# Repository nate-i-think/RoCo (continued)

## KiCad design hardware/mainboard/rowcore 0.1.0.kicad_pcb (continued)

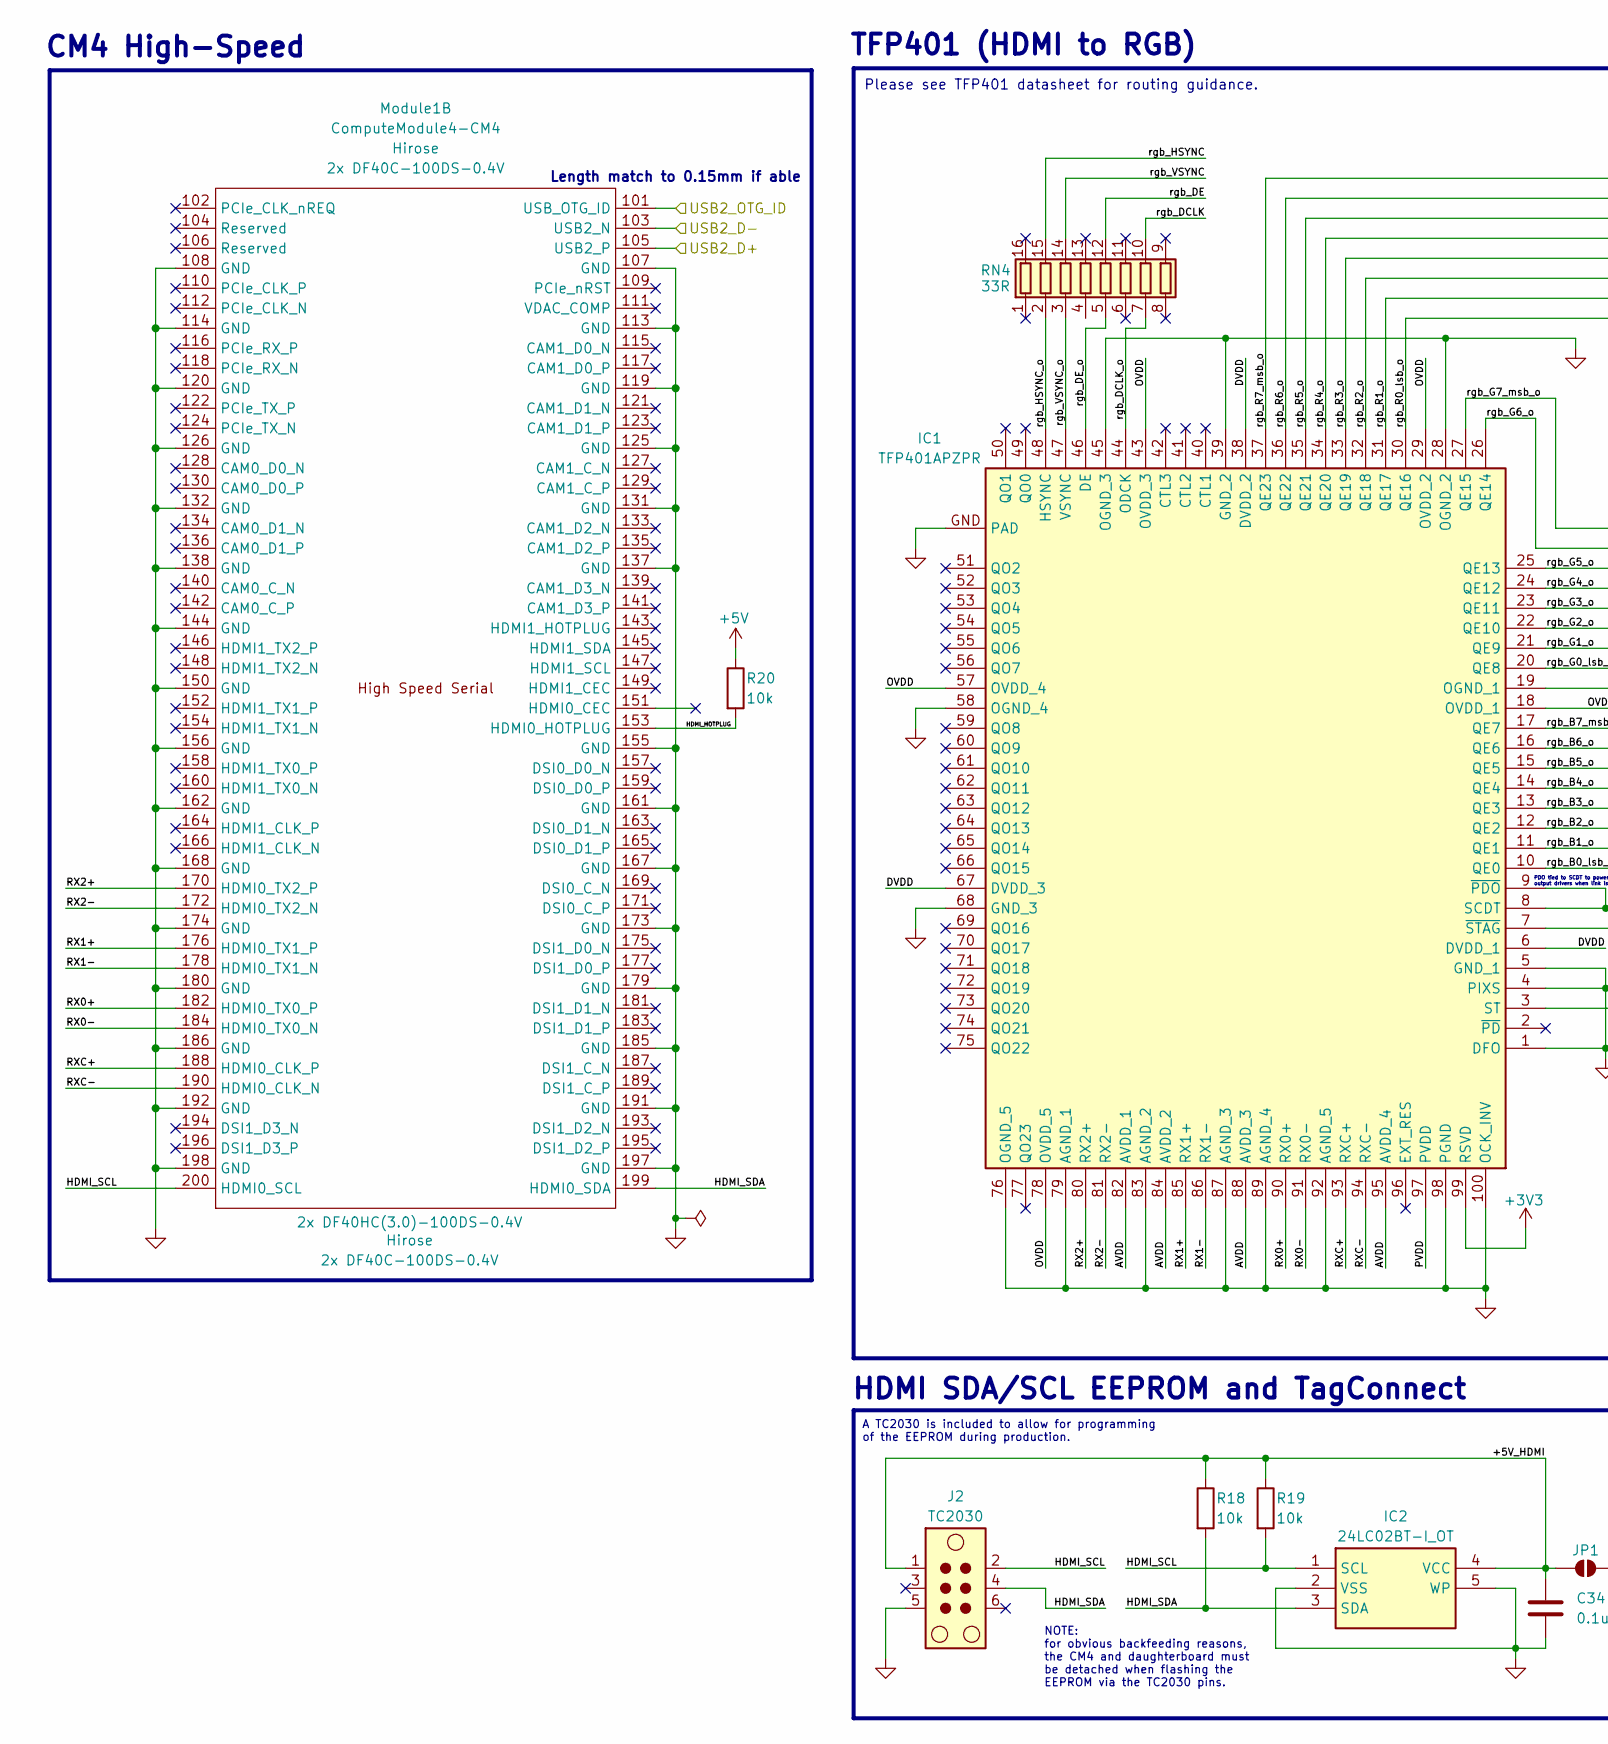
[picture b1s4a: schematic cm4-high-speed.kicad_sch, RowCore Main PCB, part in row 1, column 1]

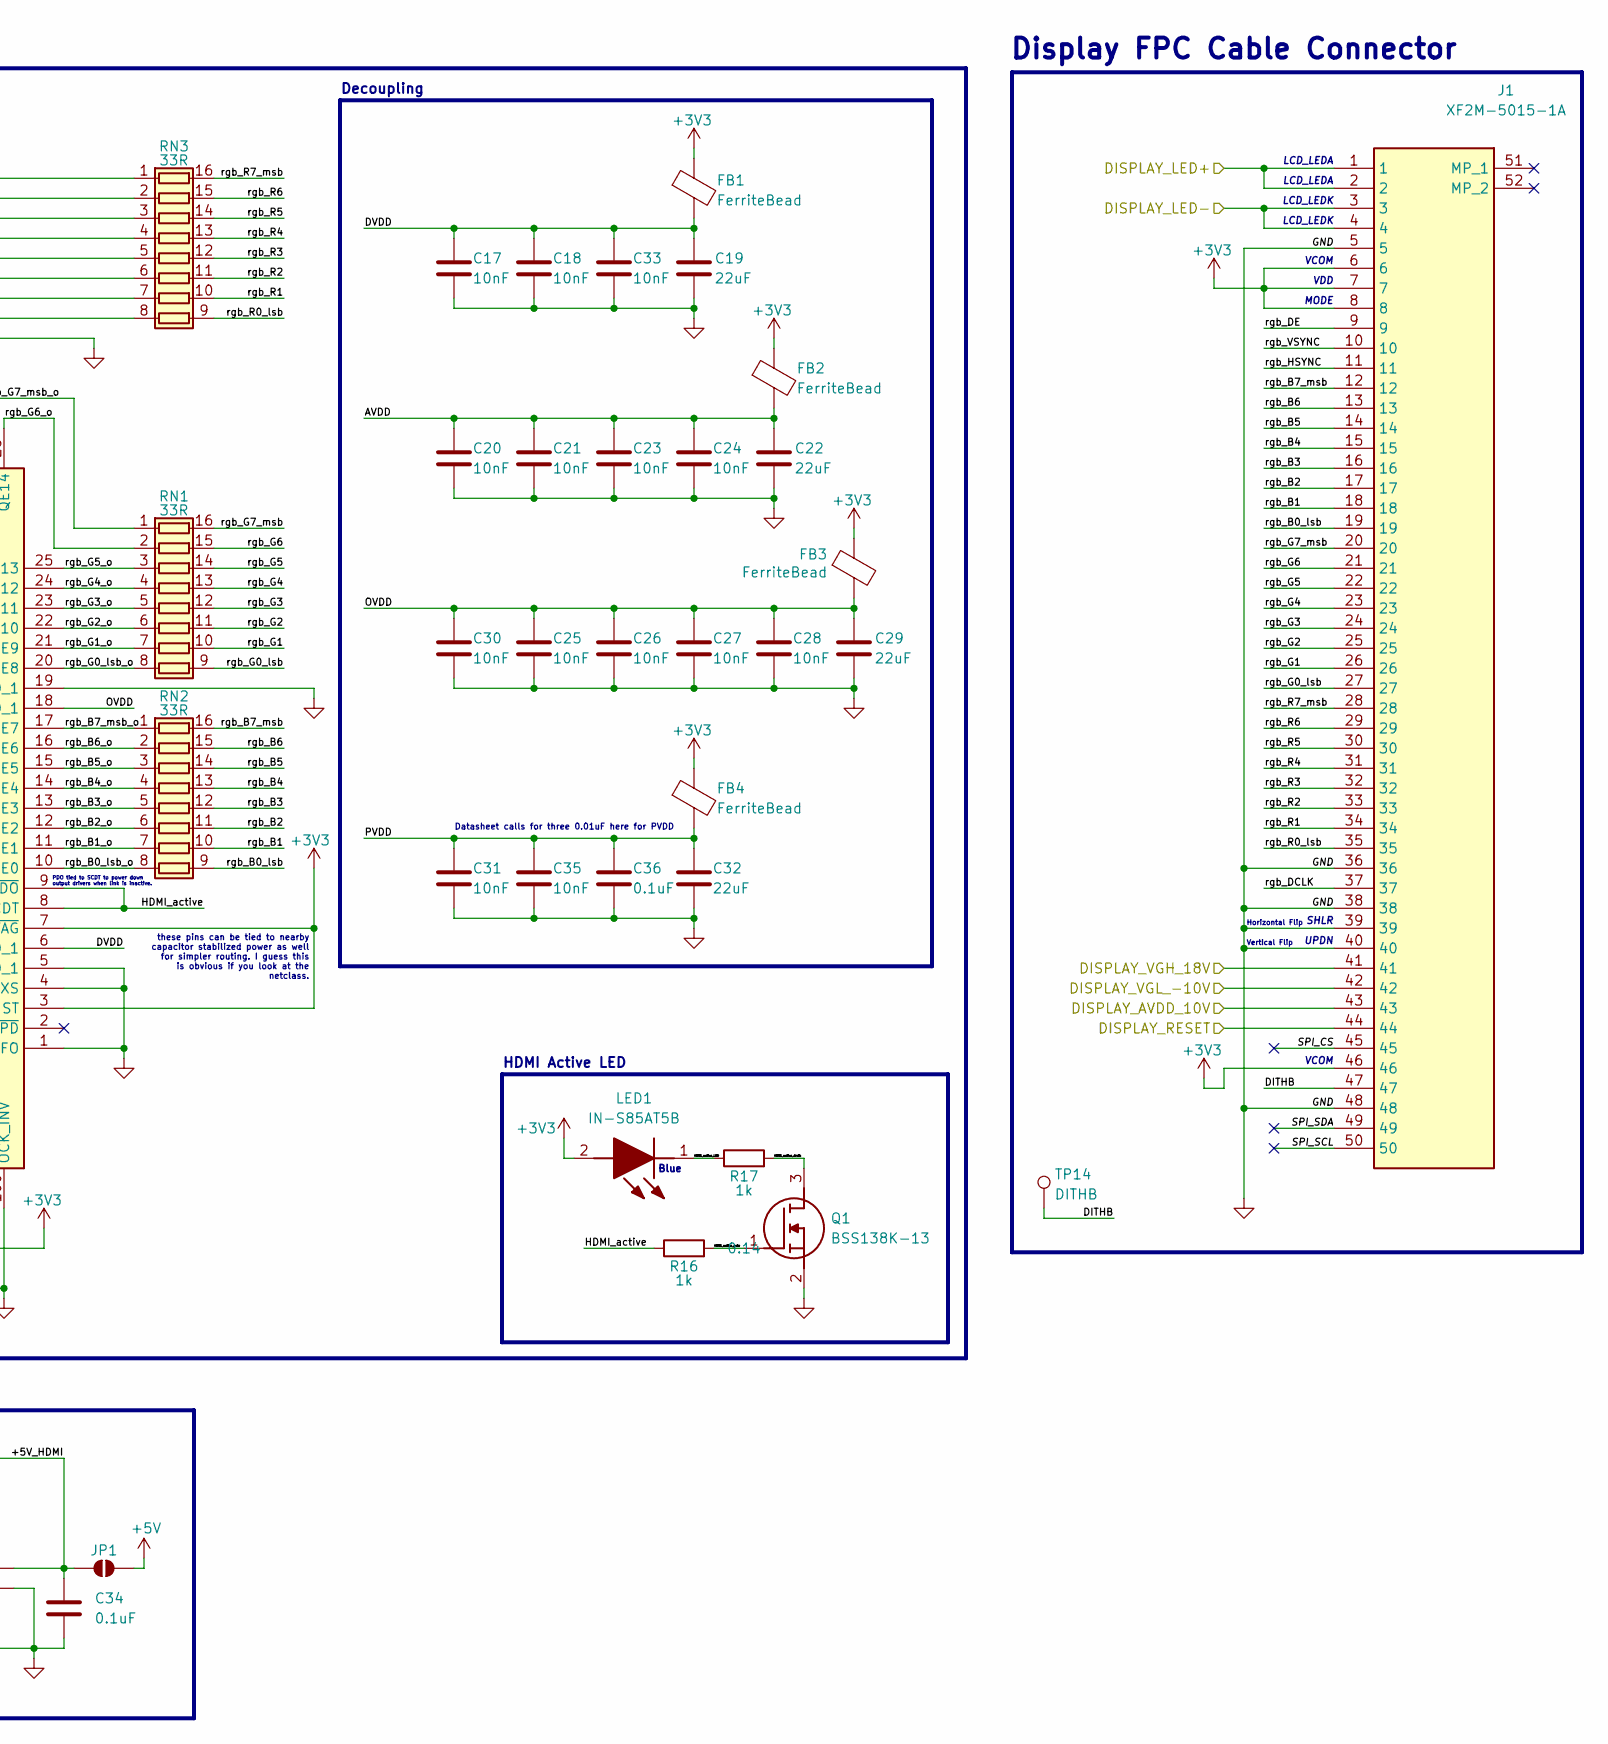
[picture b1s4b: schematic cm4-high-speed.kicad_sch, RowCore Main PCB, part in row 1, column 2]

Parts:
C17, C18, C20, C21, C23, C24, C25, C26, C27, C28, C30, C31, C33, C35: 10nF; C_0402_1005Metric
C19, C22, C29, C32: 22uF; C_1206_3216Metric
C34, C36: 0.1uF; C_0402_1005Metric
FB1, FB2, FB3, FB4: FerriteBead; BEADC1608X95N
IC1: TFP401APZPR; QFP50P1600X1600X120-100N; Mouser Part Number 595-TFP401APZPR
IC2: 24LC02BT-I_OT; SOT95P270X145-5N; Mouser Part Number 579-24LC02BT-I/OT
J1: XF2M-5015-1A; XF2M50151A; Mouser Part Number 653-XF2M-5015-1A
J2: TC2030; Tag-Connect_TC2030-IDC-NL_2x03_P1.27mm_Vertical
JP1: SolderJumper_2_Open; SolderJumper-2_P1.3mm_Open_RoundedPad1.0x1.5mm
LED1: IN-S85AT5B; LEDC2012X110N; Mouser Part Number 743-IN-S85AT5B
Module1: ComputeModule4-CM4; Raspberry-Pi-4-Compute-Module; MPN 2x DF40C-100DS-0.4V; Digi-Key_PN 2x H11615CT-ND
Q1: BSS138K-13; SOT96P240X110-3N; Mouser Part Number 621-BSS138K-13
R16, R17: 1k; R_0402_1005Metric
R18, R19, R20: 10k; R_0402_1005Metric
RN1, RN2, RN3, RN4: 33R; EXBU2H; Manufacturer Part Number EXB-U2H330JV
TP14: DITHB; TestPoint_Pad_D1.5mm

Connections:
+5V: JP1.1 (A), R20.1; also elsewhere on the board
/CM4 Lite GPIO/DISPLAY_RESET: J1.44; also elsewhere on the board
/CM4 Lite High Speed/+5V_HDMI: C34.1, IC2.4 (VCC), J2.1, JP1.2 (B), R18.1, R19.1; also elsewhere on the board
/CM4 Lite High Speed/AVDD: C20.1, C21.1, C22.1, C23.1, C24.1, FB2.2, IC1.82 (AVDD_1), IC1.84 (AVDD_2), IC1.88 (AVDD_3), IC1.95 (AVDD_4)
/CM4 Lite High Speed/DISPLAY_LED+: J1.1, J1.2; also elsewhere on the board
/CM4 Lite High Speed/DISPLAY_LED-: J1.3, J1.4; also elsewhere on the board
/CM4 Lite High Speed/DISPLAY_VGH_18V: J1.41; also elsewhere on the board
/CM4 Lite High Speed/DISPLAY_VGL_-10V: J1.42; also elsewhere on the board
/CM4 Lite High Speed/DITHB: J1.47, TP14.1
/CM4 Lite High Speed/DVDD: C17.1, C18.1, C19.1, C33.1, FB1.2, IC1.6 (DVDD_1), IC1.38 (DVDD_2), IC1.67 (DVDD_3)
/CM4 Lite High Speed/HDMI_HOTPLUG: Module1.153 (HDMI0_HOTPLUG), R20.2
/CM4 Lite High Speed/HDMI_SCL: IC2.1 (SCL), J2.2, Module1.200 (HDMI0_SCL), R19.2; also elsewhere on the board
/CM4 Lite High Speed/HDMI_SDA: IC2.3 (SDA), J2.4, Module1.199 (HDMI0_SDA), R18.2; also elsewhere on the board
/CM4 Lite High Speed/HDMI_active: IC1.8 (SCDT), IC1.9 (~PDO), R16.1
/CM4 Lite High Speed/HDMI_active_LED: LED1.1 (K), R17.1
/CM4 Lite High Speed/HDMI_active_drain: Q1.3 (D), R17.2
/CM4 Lite High Speed/HDMI_active_gate: Q1.1 (G), R16.2
/CM4 Lite High Speed/OVDD: C25.1, C26.1, C27.1, C28.1, C29.1, C30.1, FB3.2, IC1.18 (OVDD_1), IC1.29 (OVDD_2), IC1.43 (OVDD_3), IC1.57 (OVDD_4), IC1.78 (OVDD_5)
/CM4 Lite High Speed/PVDD: C31.1, C32.1, C35.1, C36.1, FB4.2, IC1.97 (PVDD)
/CM4 Lite High Speed/RX0+: IC1.90 (RX0+), Module1.182 (HDMI0_TX0_P)
/CM4 Lite High Speed/RX0-: IC1.91 (RX0-), Module1.184 (HDMI0_TX0_N)
/CM4 Lite High Speed/RX1+: IC1.85 (RX1+), Module1.176 (HDMI0_TX1_P)
/CM4 Lite High Speed/RX1-: IC1.86 (RX1-), Module1.178 (HDMI0_TX1_N)
/CM4 Lite High Speed/RX2+: IC1.80 (RX2+), Module1.170 (HDMI0_TX2_P)
/CM4 Lite High Speed/RX2-: IC1.81 (RX2-), Module1.172 (HDMI0_TX2_N)
/CM4 Lite High Speed/RXC+: IC1.93 (RXC+), Module1.188 (HDMI0_CLK_P)
/CM4 Lite High Speed/RXC-: IC1.94 (RXC-), Module1.190 (HDMI0_CLK_N)
/CM4 Lite High Speed/SPI_CS: J1.45
/CM4 Lite High Speed/SPI_SCL: J1.50
/CM4 Lite High Speed/SPI_SDA: J1.49
/CM4 Lite High Speed/USB2_OTG_ID: Module1.101 (USB_OTG_ID)
/CM4 Lite High Speed/rgb_B0_lsb: J1.19, RN2.9 (R8.2)
/CM4 Lite High Speed/rgb_B0_lsb_o: IC1.10 (QE0), RN2.8 (R8.1)
/CM4 Lite High Speed/rgb_B1: J1.18, RN2.10 (R7.2)
/CM4 Lite High Speed/rgb_B1_o: IC1.11 (QE1), RN2.7 (R7.1)
/CM4 Lite High Speed/rgb_B2: J1.17, RN2.11 (R6.2)
/CM4 Lite High Speed/rgb_B2_o: IC1.12 (QE2), RN2.6 (R6.1)
/CM4 Lite High Speed/rgb_B3: J1.16, RN2.12 (R5.2)
/CM4 Lite High Speed/rgb_B3_o: IC1.13 (QE3), RN2.5 (R5.1)
/CM4 Lite High Speed/rgb_B4: J1.15, RN2.13 (R4.2)
/CM4 Lite High Speed/rgb_B4_o: IC1.14 (QE4), RN2.4 (R4.1)
/CM4 Lite High Speed/rgb_B5: J1.14, RN2.14 (R3.2)
/CM4 Lite High Speed/rgb_B5_o: IC1.15 (QE5), RN2.3 (R3.1)
/CM4 Lite High Speed/rgb_B6: J1.13, RN2.15 (R2.2)
/CM4 Lite High Speed/rgb_B6_o: IC1.16 (QE6), RN2.2 (R2.1)
/CM4 Lite High Speed/rgb_B7_msb: J1.12, RN2.16 (R1.2)
/CM4 Lite High Speed/rgb_B7_msb_o: IC1.17 (QE7), RN2.1 (R1.1)
/CM4 Lite High Speed/rgb_DCLK: J1.37, RN4.10 (R7.2)
/CM4 Lite High Speed/rgb_DCLK_o: IC1.44 (ODCK), RN4.7 (R7.1)
/CM4 Lite High Speed/rgb_DE: J1.9, RN4.12 (R5.2)
/CM4 Lite High Speed/rgb_DE_o: IC1.46 (DE), RN4.5 (R5.1)
/CM4 Lite High Speed/rgb_G0_lsb: J1.27, RN1.9 (R8.2)
/CM4 Lite High Speed/rgb_G0_lsb_o: IC1.20 (QE8), RN1.8 (R8.1)
/CM4 Lite High Speed/rgb_G1: J1.26, RN1.10 (R7.2)
/CM4 Lite High Speed/rgb_G1_o: IC1.21 (QE9), RN1.7 (R7.1)
/CM4 Lite High Speed/rgb_G2: J1.25, RN1.11 (R6.2)
/CM4 Lite High Speed/rgb_G2_o: IC1.22 (QE10), RN1.6 (R6.1)
/CM4 Lite High Speed/rgb_G3: J1.24, RN1.12 (R5.2)
/CM4 Lite High Speed/rgb_G3_o: IC1.23 (QE11), RN1.5 (R5.1)
/CM4 Lite High Speed/rgb_G4: J1.23, RN1.13 (R4.2)
/CM4 Lite High Speed/rgb_G4_o: IC1.24 (QE12), RN1.4 (R4.1)
/CM4 Lite High Speed/rgb_G5: J1.22, RN1.14 (R3.2)
/CM4 Lite High Speed/rgb_G5_o: IC1.25 (QE13), RN1.3 (R3.1)
/CM4 Lite High Speed/rgb_G6: J1.21, RN1.15 (R2.2)
/CM4 Lite High Speed/rgb_G6_o: IC1.26 (QE14), RN1.2 (R2.1)
/CM4 Lite High Speed/rgb_G7_msb: J1.20, RN1.16 (R1.2)
/CM4 Lite High Speed/rgb_G7_msb_o: IC1.27 (QE15), RN1.1 (R1.1)
/CM4 Lite High Speed/rgb_HSYNC: J1.11, RN4.15 (R2.2)
/CM4 Lite High Speed/rgb_HSYNC_o: IC1.48 (HSYNC), RN4.2 (R2.1)
/CM4 Lite High Speed/rgb_R0_lsb: J1.35, RN3.9 (R8.2)
/CM4 Lite High Speed/rgb_R0_lsb_o: IC1.30 (QE16), RN3.8 (R8.1)
/CM4 Lite High Speed/rgb_R1: J1.34, RN3.10 (R7.2)
/CM4 Lite High Speed/rgb_R1_o: IC1.31 (QE17), RN3.7 (R7.1)
/CM4 Lite High Speed/rgb_R2: J1.33, RN3.11 (R6.2)
/CM4 Lite High Speed/rgb_R2_o: IC1.32 (QE18), RN3.6 (R6.1)
/CM4 Lite High Speed/rgb_R3: J1.32, RN3.12 (R5.2)
/CM4 Lite High Speed/rgb_R3_o: IC1.33 (QE19), RN3.5 (R5.1)
/CM4 Lite High Speed/rgb_R4: J1.31, RN3.13 (R4.2)
/CM4 Lite High Speed/rgb_R4_o: IC1.34 (QE20), RN3.4 (R4.1)
/CM4 Lite High Speed/rgb_R5: J1.30, RN3.14 (R3.2)
/CM4 Lite High Speed/rgb_R5_o: IC1.35 (QE21), RN3.3 (R3.1)
/CM4 Lite High Speed/rgb_R6: J1.29, RN3.15 (R2.2)
/CM4 Lite High Speed/rgb_R6_o: IC1.36 (QE22), RN3.2 (R2.1)
/CM4 Lite High Speed/rgb_R7_msb: J1.28, RN3.16 (R1.2)
/CM4 Lite High Speed/rgb_R7_msb_o: IC1.37 (QE23), RN3.1 (R1.1)
/CM4 Lite High Speed/rgb_VSYNC: J1.10, RN4.14 (R3.2)
/CM4 Lite High Speed/rgb_VSYNC_o: IC1.47 (VSYNC), RN4.3 (R3.1)
/USB_D+: Module1.105 (USB2_P); also elsewhere on the board
/USB_D-: Module1.103 (USB2_N); also elsewhere on the board
/Voltage Generation/DISPLAY_AVDD_10V: J1.43; also elsewhere on the board

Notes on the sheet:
Vertical Flip
VDD
MODE
Datasheet calls for three 0.01uF here for PVDD
LCD_LEDA
VCOM
Blue
A TC2030 is included to allow for programming of the EEPROM during production.
PDO tied to SCDT to power down output drivers when link is inactive.
Please see TFP401 datasheet for routing guidance.
SHLR
Horizontal Flip
Display FPC Cable Connector
Length match to 0.15mm if able
TFP401 (HDMI to RGB)
LCD_LEDK
Decoupling
NOTE: for obvious backfeeding reasons, the CM4 and daughterboard must be detached when flashing the EEPROM via the TC2030 pins.
CM4 High-Speed
HDMI SDA/SCL EEPROM and TagConnect
HDMI Active LED
UPDN
these pins can be tied to nearby capacitor stabilized power as well for simpler routing. I guess this is obvious if you look at the netclass.

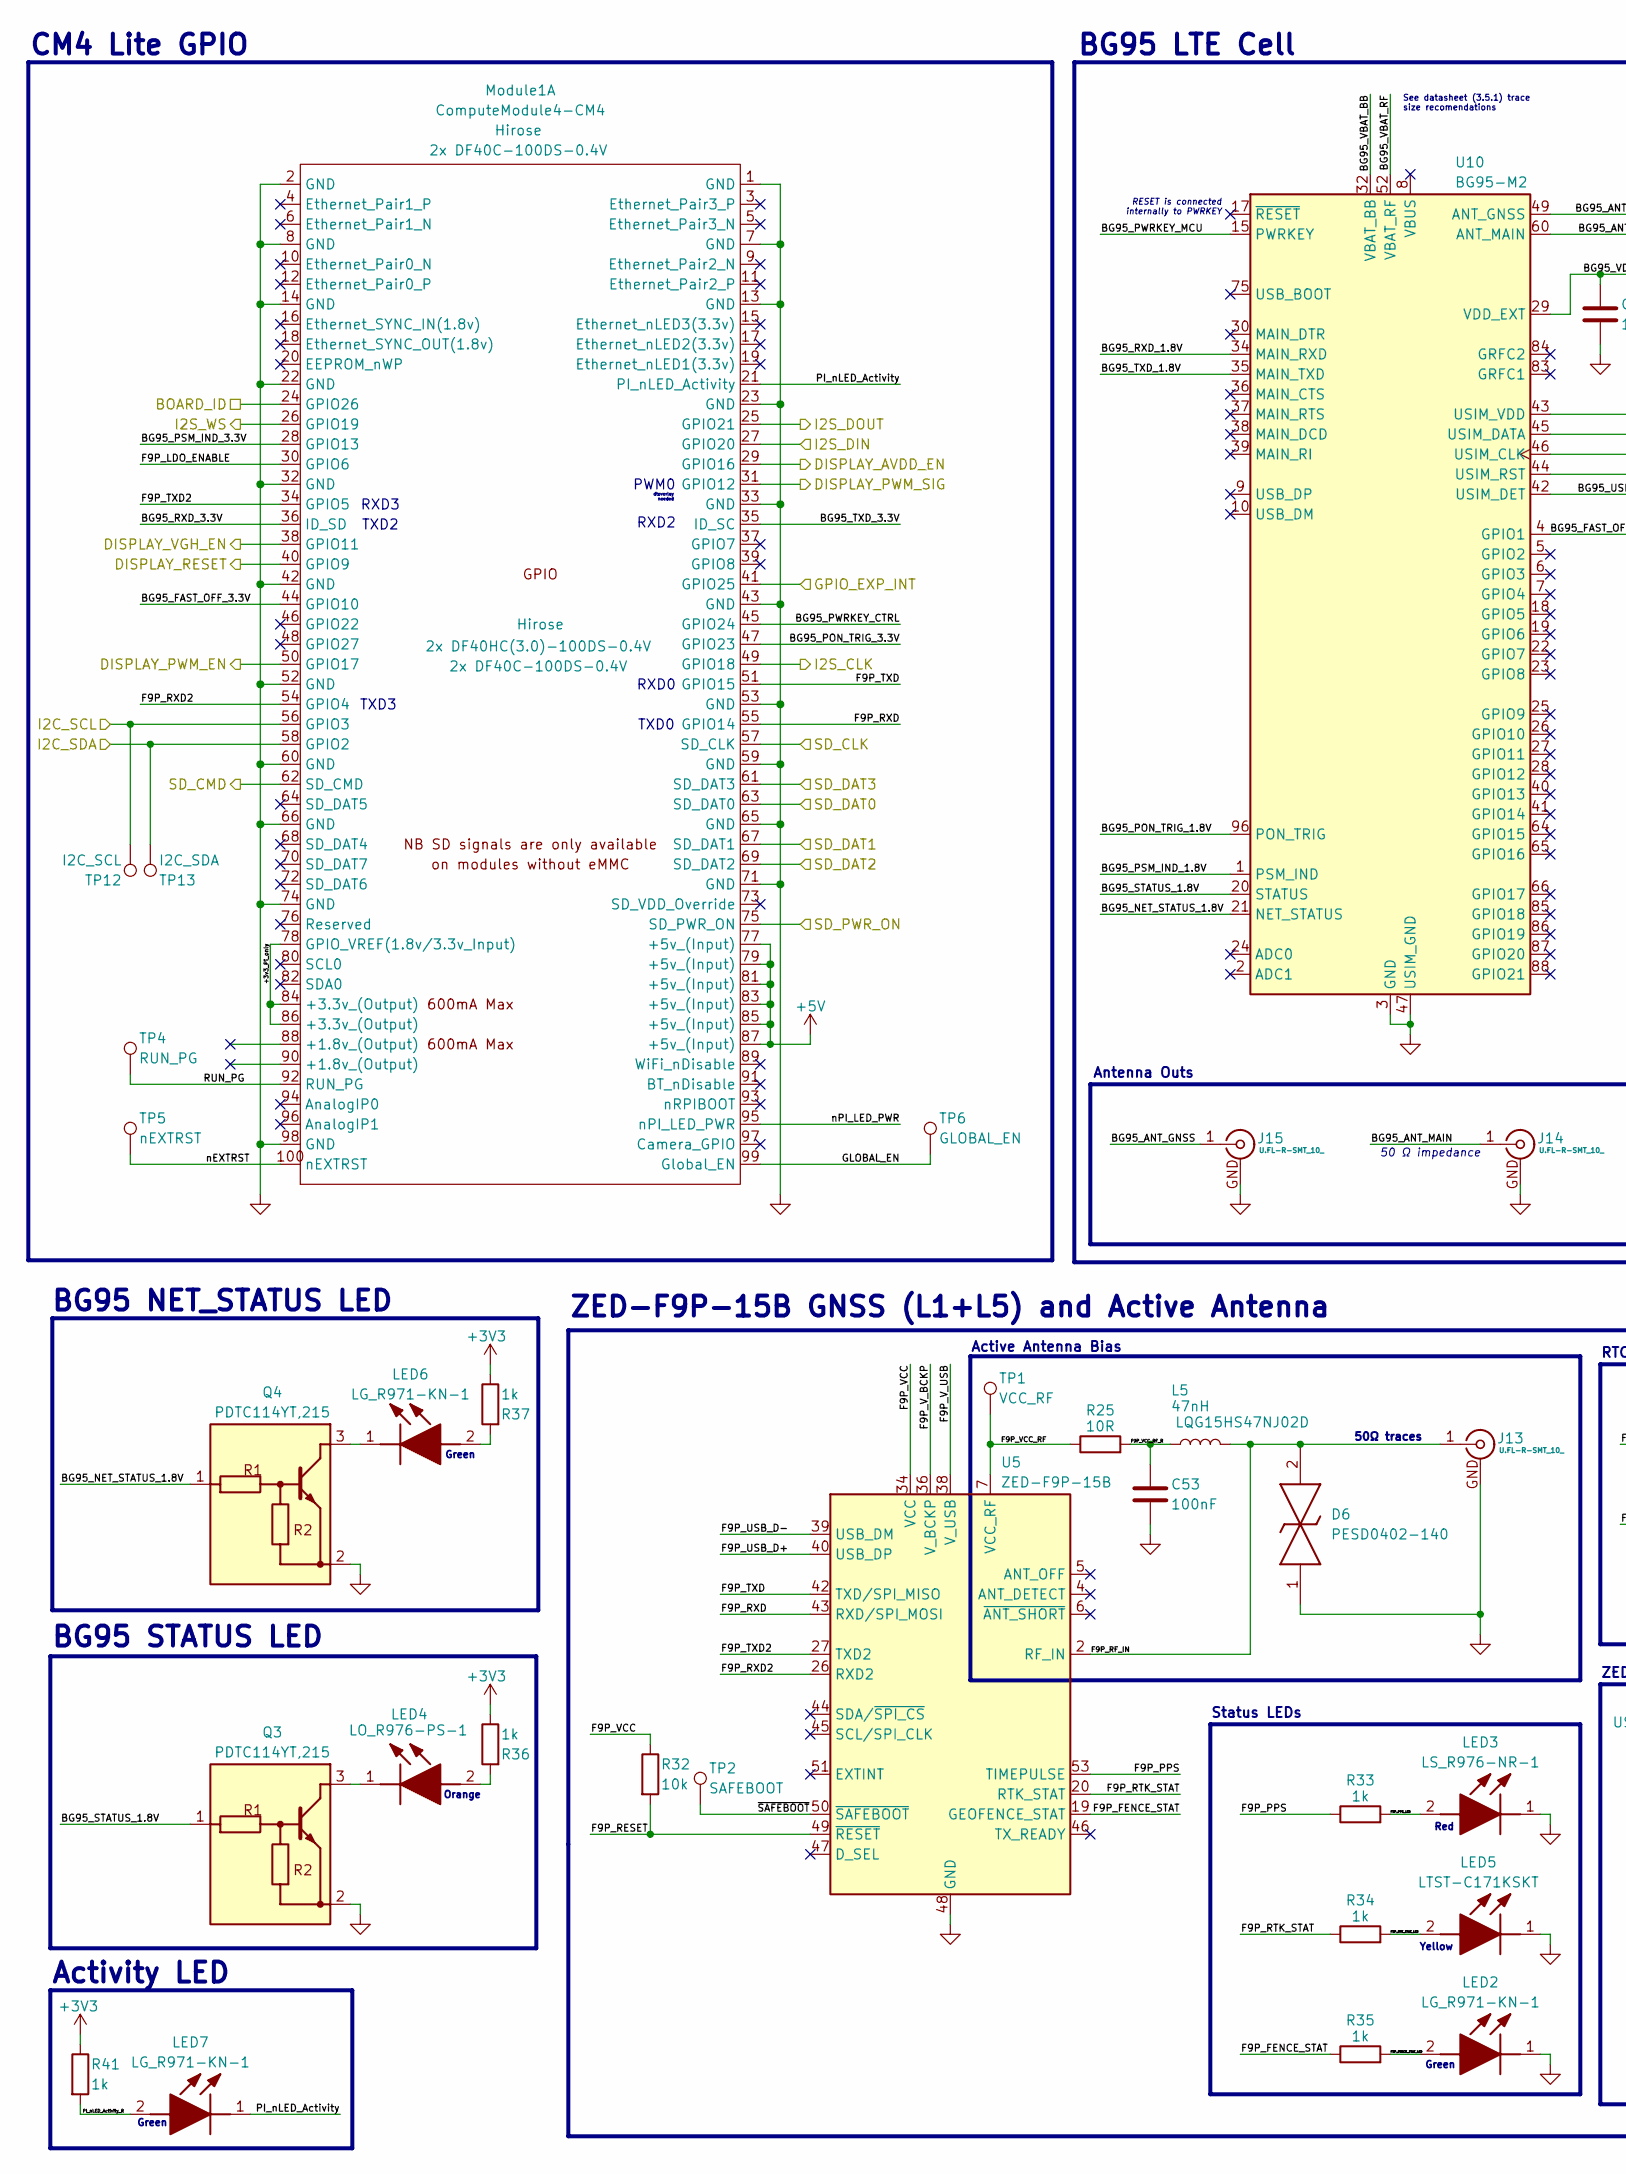
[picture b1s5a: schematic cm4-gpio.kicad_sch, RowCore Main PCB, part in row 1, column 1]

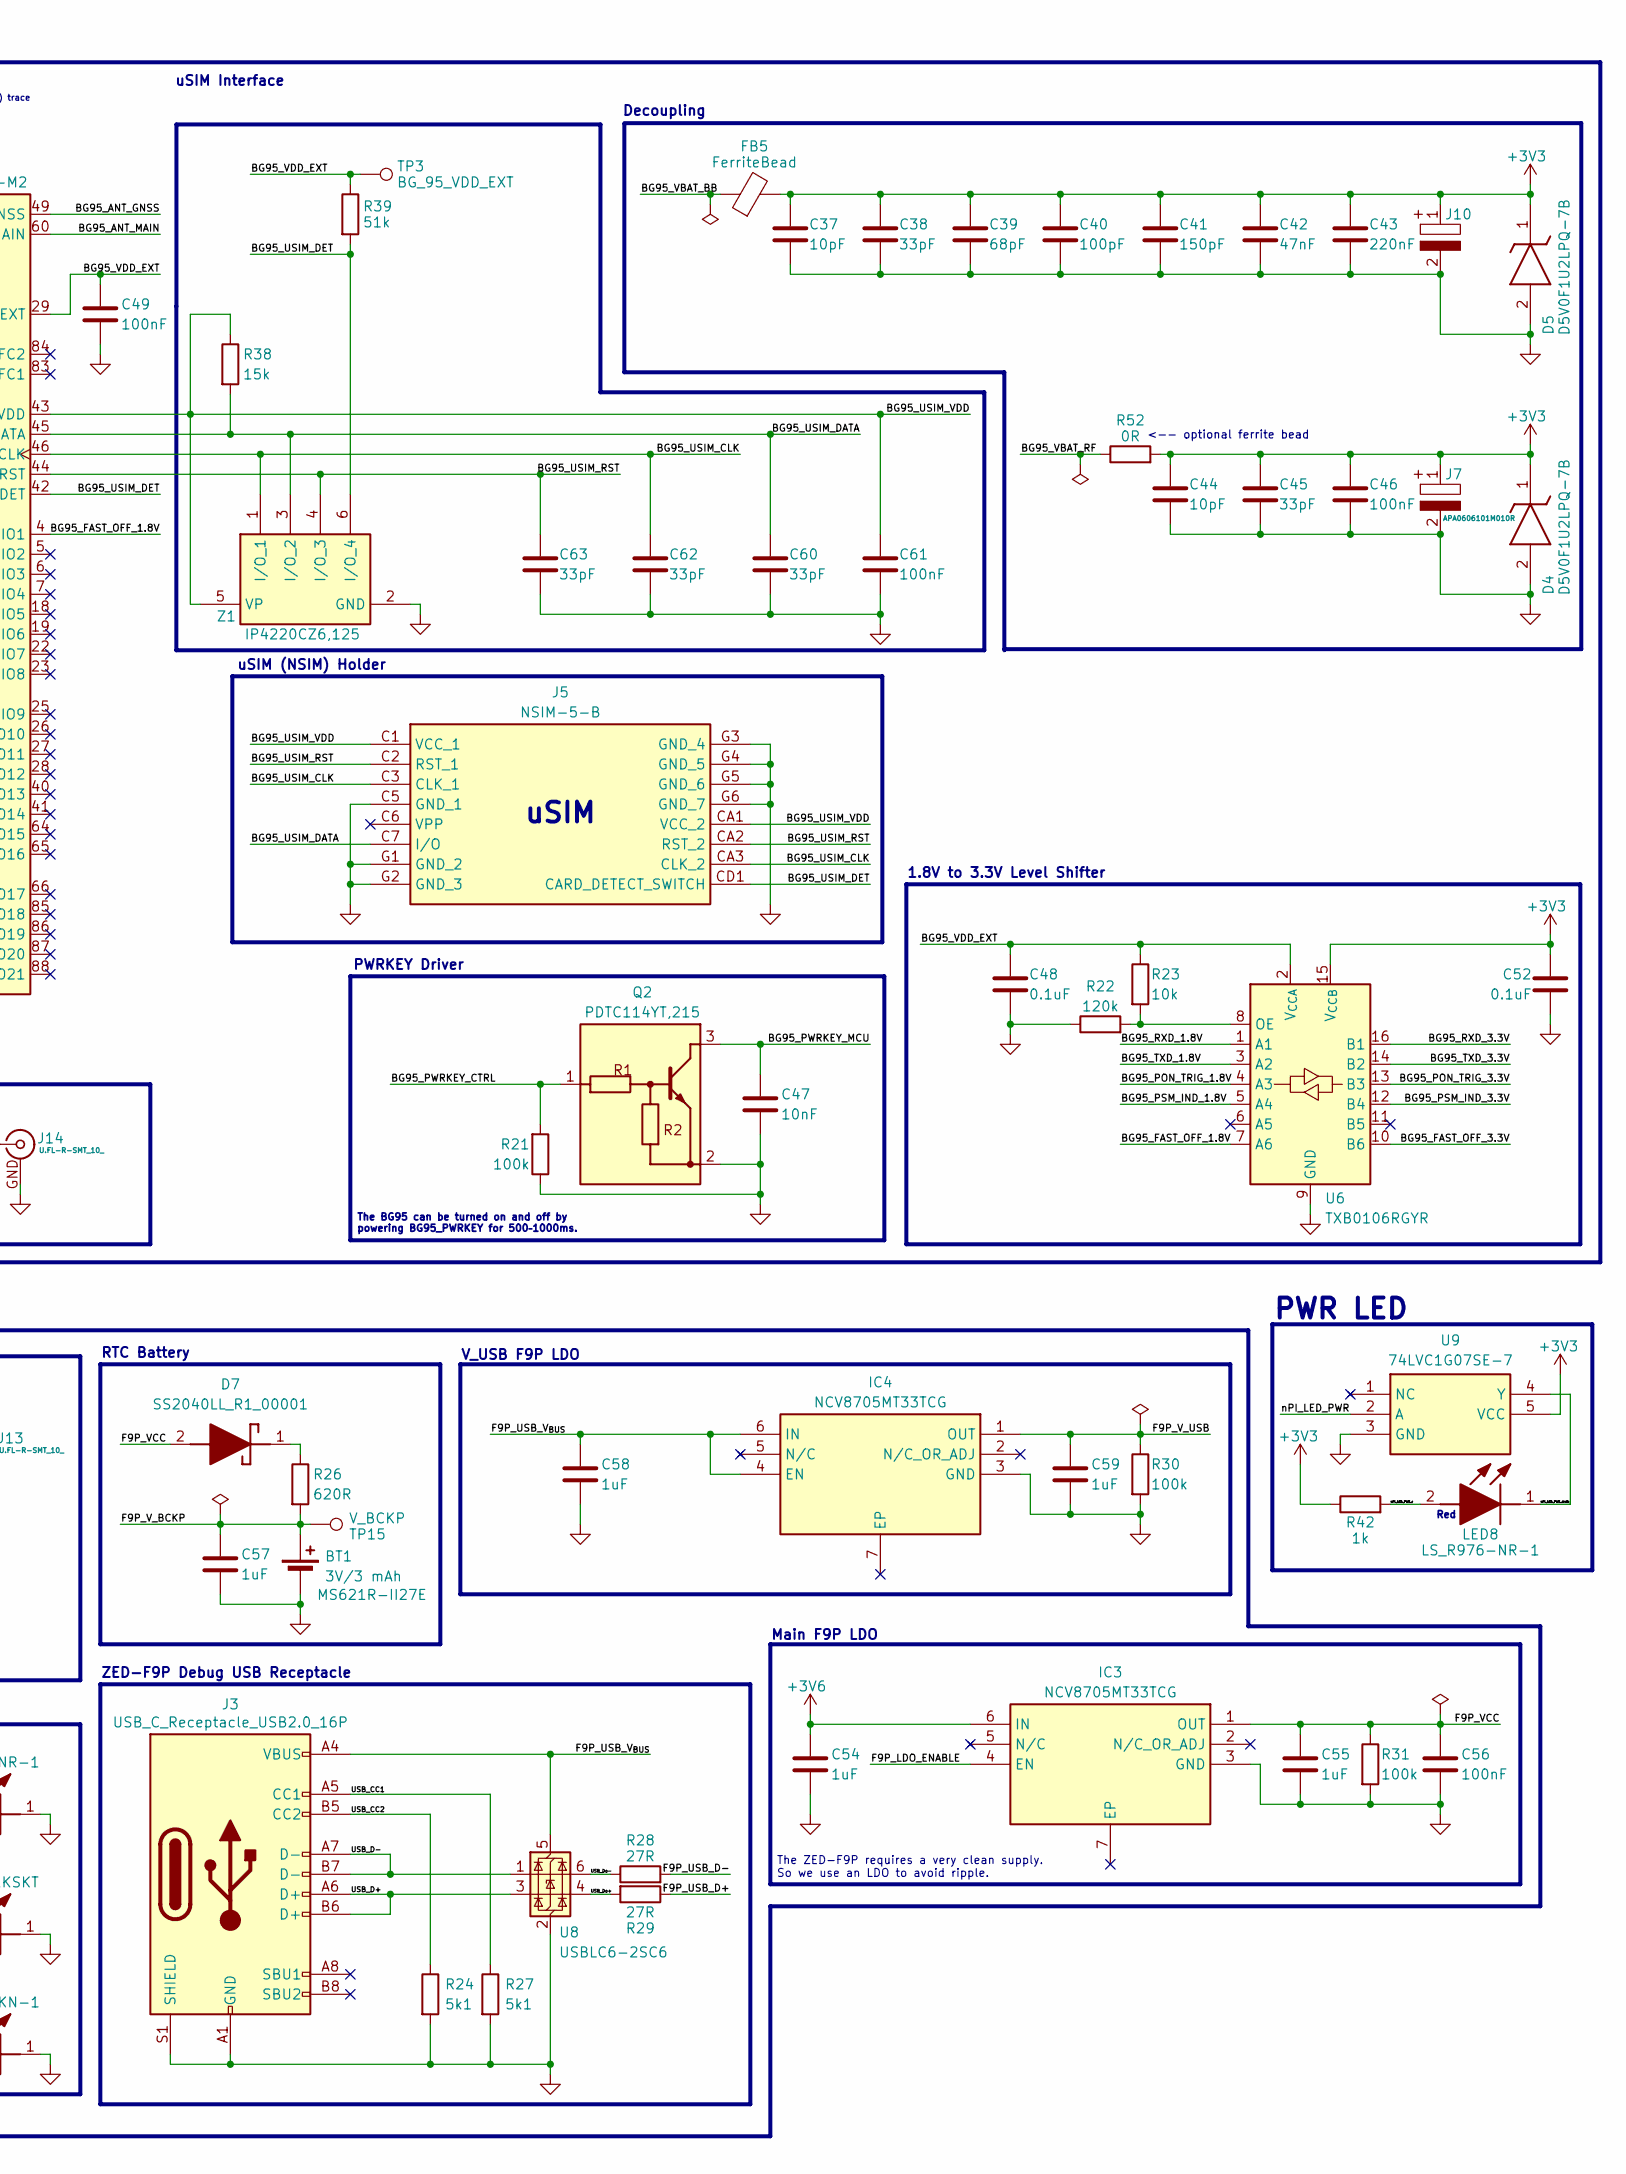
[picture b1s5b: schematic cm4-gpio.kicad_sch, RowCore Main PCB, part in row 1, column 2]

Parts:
BT1: 3V/3 mAh; MS621R; Manufacturer Part Number MS621R-II27E
C37, C44: 10pF; C_0402_1005Metric
C38, C45, C60, C62, C63: 33pF; C_0402_1005Metric
C39: 68pF; C_0402_1005Metric
C40: 100pF; C_0402_1005Metric
C41: 150pF; C_0402_1005Metric
C42: 47nF; C_0402_1005Metric
C43: 220nF; C_0402_1005Metric
C46, C49, C53, C56, C61: 100nF; C_0402_1005Metric
C47: 10nF; C_0402_1005Metric
C48, C52: 0.1uF; C_0402_1005Metric
C54, C55, C57, C58, C59: 1uF; C_0805_2012Metric
D4, D5: D5V0F1U2LPQ-7B; D5V0F1U2LPQ7B; Mouser Part Number 621-D5V0F1U2LPQ-7B
D6: PESD0402-140; DIONC1005X43N; Mouser Part Number 650-PESD0402-140
D7: SS2040LL_R1_00001; SODFL3618X110N; Mouser Part Number 241-SS2040LLR100001
FB5: FerriteBead; BEADC1608X75N
IC3, IC4: NCV8705MT33TCG; SON65P200X200X80-7N; Mouser Part Number 863-NCV8705MT33TCG
J3: USB_C_Receptacle_USB2.0_16P; USB_C_Receptacle_GCT_USB4085
J5: NSIM-5-B; NSIM5B; Mouser Part Number 179-NSIM-5-B
J7, J10: APA0606101M010R; CAPAE660X650N; Mouser Part Number 581-APA0606101M010R
J13, J14, J15: U.FL-R-SMT_10_; UFLRSMT10; Mouser Part Number 798-U.FL-R-SMT10
L5: 47nH; LQG15WH0N7B02D; Manufacturer Part Number LQG15HS47NJ02D
LED2, LED6, LED7: LG_R971-KN-1; LEDC2012X80N; Mouser Part Number 720-LGR971-KN-1
LED3, LED8: LS_R976-NR-1; LEDC2012X40N; Mouser Part Number 720-LSR976-NR-1
LED4: LO_R976-PS-1; LEDC2012X90N; Mouser Part Number 720-LOR976-PS-1
LED5: LTST-C171KSKT; LTSTC171KSKT; Mouser Part Number 859-LTST-C171KSKT
Module1: ComputeModule4-CM4; Raspberry-Pi-4-Compute-Module; MPN 2x DF40C-100DS-0.4V; Digi-Key_PN 2x H11615CT-ND
Q2, Q3, Q4: PDTC114YT,215; SOT95P230X110-3N; Mouser Part Number 771-PDTC114YTT/R
R21, R30, R31: 100k; R_0402_1005Metric
R22: 120k; R_0402_1005Metric
R23, R32: 10k; R_0402_1005Metric
R24, R27: 5k1; R_0402_1005Metric
R25: 10R; R_0402_1005Metric
R26: 620R; R_0402_1005Metric
R28, R29: 27R; R_0402_1005Metric
R33, R34, R35, R36, R37, R41, R42: 1k; R_0402_1005Metric
R38: 15k; R_0402_1005Metric
R39: 51k; R_0402_1005Metric
R52: 0R; R_0603_1608Metric
TP1: VCC_RF; TestPoint_Pad_D1.5mm
TP2: SAFEBOOT; TestPoint_Pad_D1.5mm
TP3: BG_95_VDD_EXT; TestPoint_Pad_D1.5mm
TP4: RUN_PG; TestPoint_Pad_D1.5mm
TP5: nEXTRST; TestPoint_Pad_D1.5mm
TP6: GLOBAL_EN; TestPoint_Pad_D1.5mm
TP12: I2C_SCL; TestPoint_Pad_D1.5mm
TP13: I2C_SDA; TestPoint_Pad_D1.5mm
TP15: V_BCKP; TestPoint_Pad_D1.5mm
U5: ZED-F9P-15B; ublox_ZED
U6: TXB0106RGYR; Texas_RGY_R-PVQFN-N16_EP2.05x2.55mm; Manufacturer Part Number TXB0106RGYR
U8: USBLC6-2SC6; SOT-23-6
U9: 74LVC1G07SE-7; SOT65P210X110-5N; Mouser Part Number 621-74LVC1G07SE-7
U10: BG95-M2; Quectel_BG95
Z1: IP4220CZ6,125; SOT95P275X110-6N; Mouser Part Number 771-IP4220CZ6-T/R

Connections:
+3V6: C54.1, IC3.6 (IN); also elsewhere on the board
+5V: Module1.77 (+5v_(Input)), Module1.79 (+5v_(Input)), Module1.81 (+5v_(Input)), Module1.83 (+5v_(Input)), Module1.85 (+5v_(Input)), Module1.87 (+5v_(Input)); also elsewhere on the board
/Assorted/SD_CLK: Module1.57 (SD_CLK); also elsewhere on the board
/Assorted/SD_CMD: Module1.62 (SD_CMD); also elsewhere on the board
/Assorted/SD_DAT0: Module1.63 (SD_DAT0); also elsewhere on the board
/Assorted/SD_DAT1: Module1.67 (SD_DAT1); also elsewhere on the board
/Assorted/SD_DAT2: Module1.69 (SD_DAT2); also elsewhere on the board
/Assorted/SD_DAT3: Module1.61 (SD_DAT3); also elsewhere on the board
/Assorted/SD_PWR_ON: Module1.75 (SD_PWR_ON); also elsewhere on the board
/BOARD_ID: Module1.24 (GPIO26); also elsewhere on the board
/CM4 Lite GPIO/+3v3_Pi_only: Module1.78 (GPIO_VREF(1.8v/3.3v_Input)), Module1.84 (+3.3v_(Output)), Module1.86 (+3.3v_(Output))
/CM4 Lite GPIO/BG95_ANT_GNSS: J15.1, U10.49 (ANT_GNSS)
/CM4 Lite GPIO/BG95_ANT_MAIN: J14.1, U10.60 (ANT_MAIN)
/CM4 Lite GPIO/BG95_FAST_OFF_1.8V: U6.7 (A6), U10.4 (GPIO1)
/CM4 Lite GPIO/BG95_FAST_OFF_3.3V: Module1.44 (GPIO10), U6.10 (B6)
/CM4 Lite GPIO/BG95_NET_STATUS_1.8V: Q4.1 (B), U10.21 (NET_STATUS)
/CM4 Lite GPIO/BG95_PON_TRIG_1.8V: U6.4 (A3), U10.96 (PON_TRIG)
/CM4 Lite GPIO/BG95_PON_TRIG_3.3V: Module1.47 (GPIO23), U6.13 (B3)
/CM4 Lite GPIO/BG95_PSM_IND_1.8V: U6.5 (A4), U10.1 (PSM_IND)
/CM4 Lite GPIO/BG95_PSM_IND_3.3V: Module1.28 (GPIO13), U6.12 (B4)
/CM4 Lite GPIO/BG95_PWRKEY_CTRL: Module1.45 (GPIO24), Q2.1 (B), R21.2
/CM4 Lite GPIO/BG95_PWRKEY_MCU: C47.1, Q2.3 (C), U10.15 (PWRKEY)
/CM4 Lite GPIO/BG95_RXD_1.8V: U6.1 (A1), U10.34 (MAIN_RXD)
/CM4 Lite GPIO/BG95_RXD_3.3V: Module1.36 (ID_SD), U6.16 (B1)
/CM4 Lite GPIO/BG95_STATUS_1.8V: Q3.1 (B), U10.20 (STATUS)
/CM4 Lite GPIO/BG95_TXD_1.8V: U6.3 (A2), U10.35 (MAIN_TXD)
/CM4 Lite GPIO/BG95_TXD_3.3V: Module1.35 (ID_SC), U6.14 (B2)
/CM4 Lite GPIO/BG95_USIM_CLK: C62.1, J5.C3 (CLK_1), J5.CA3 (CLK_2), U10.46 (USIM_CLK), Z1.1 (I/O_1)
/CM4 Lite GPIO/BG95_USIM_DATA: C60.1, J5.C7 (I/O), R38.2, U10.45 (USIM_DATA), Z1.3 (I/O_2)
/CM4 Lite GPIO/BG95_USIM_DET: J5.CD1 (CARD_DETECT_SWITCH), R39.2, U10.42 (USIM_DET), Z1.6 (I/O_4)
/CM4 Lite GPIO/BG95_USIM_RST: C63.1, J5.C2 (RST_1), J5.CA2 (RST_2), U10.44 (USIM_RST), Z1.4 (I/O_3)
/CM4 Lite GPIO/BG95_USIM_VDD: C61.1, J5.C1 (VCC_1), J5.CA1 (VCC_2), R38.1, U10.43 (USIM_VDD), Z1.5 (VP)
/CM4 Lite GPIO/BG95_VBAT_RF: R52.1, U10.52 (VBAT_RF), U10.53 (VBAT_RF)
/CM4 Lite GPIO/BG95_VDD_EXT: C48.1, C49.1, R23.1, R39.1, TP3.1, U6.2 (V_{CCA}), U10.29 (VDD_EXT); also elsewhere on the board
/CM4 Lite GPIO/DISPLAY_AVDD_EN: Module1.29 (GPIO16); also elsewhere on the board
/CM4 Lite GPIO/DISPLAY_PWM_EN: Module1.50 (GPIO17); also elsewhere on the board
/CM4 Lite GPIO/DISPLAY_PWM_SIG: Module1.31 (GPIO12); also elsewhere on the board
/CM4 Lite GPIO/DISPLAY_RESET: Module1.40 (GPIO9); also elsewhere on the board
/CM4 Lite GPIO/DISPLAY_VGH_EN: Module1.38 (GPIO11); also elsewhere on the board
/CM4 Lite GPIO/F9P_FENCE_STAT: R35.1, U5.19 (GEOFENCE_STAT)
/CM4 Lite GPIO/F9P_FENCE_STAT_LED: LED2.2 (A), R35.2
/CM4 Lite GPIO/F9P_LDO_ENABLE: IC3.4 (EN), Module1.30 (GPIO6)
/CM4 Lite GPIO/F9P_PPS: R33.1, U5.53 (TIMEPULSE)
/CM4 Lite GPIO/F9P_PPS_LED: LED3.2 (A), R33.2
/CM4 Lite GPIO/F9P_RESET: R32.2, U5.49 (~RESET)
/CM4 Lite GPIO/F9P_RF_IN: D6.2, J13.1, L5.2, U5.2 (RF_IN)
/CM4 Lite GPIO/F9P_RTK_STAT: R34.1, U5.20 (RTK_STAT)
/CM4 Lite GPIO/F9P_RTK_STAT_LED: LED5.2 (A), R34.2
/CM4 Lite GPIO/F9P_RXD: Module1.55 (GPIO14), U5.43 (RXD/SPI_MOSI)
/CM4 Lite GPIO/F9P_RXD2: Module1.54 (GPIO4), U5.26 (RXD2)
/CM4 Lite GPIO/F9P_TXD: Module1.51 (GPIO15), U5.42 (TXD/SPI_MISO)
/CM4 Lite GPIO/F9P_TXD2: Module1.34 (GPIO5), U5.27 (TXD2)
/CM4 Lite GPIO/F9P_USB_D+: R29.1, U5.40 (USB_DP)
/CM4 Lite GPIO/F9P_USB_D-: R28.2, U5.39 (USB_DM)
/CM4 Lite GPIO/F9P_USB_V_{BUS}: C58.1, IC4.4 (EN), IC4.6 (IN), J3.A4 (VBUS), J3.A9 (VBUS), J3.B4 (VBUS), J3.B9 (VBUS), U8.5 (VBUS)
/CM4 Lite GPIO/F9P_VCC: C55.1, C56.1, D7.2 (A), IC3.1 (OUT), R31.1, R32.1, U5.33 (VCC), U5.34 (VCC)
/CM4 Lite GPIO/F9P_VCC_RF: R25.1, TP1.1, U5.7 (VCC_RF); also elsewhere on the board
/CM4 Lite GPIO/F9P_VCC_RF_R: C53.1, L5.1, R25.2
/CM4 Lite GPIO/F9P_V_BCKP: BT1.1 (+), C57.1, R26.2, TP15.1, U5.36 (V_BCKP); also elsewhere on the board
/CM4 Lite GPIO/F9P_V_USB: C59.1, IC4.1 (OUT), R30.1, U5.38 (V_USB)
/CM4 Lite GPIO/GLOBAL_EN: Module1.99 (Global_EN), TP6.1; also elsewhere on the board
/CM4 Lite GPIO/I2S_CLK: Module1.49 (GPIO18); also elsewhere on the board
/CM4 Lite GPIO/I2S_DIN: Module1.27 (GPIO20); also elsewhere on the board
/CM4 Lite GPIO/I2S_DOUT: Module1.25 (GPIO21); also elsewhere on the board
/CM4 Lite GPIO/I2S_WS: Module1.26 (GPIO19); also elsewhere on the board
/CM4 Lite GPIO/PI_nLED_Activity: LED7.1 (K), Module1.21 (PI_nLED_Activity)
/CM4 Lite GPIO/PI_nLED_Activity_R: LED7.2 (A), R41.2
/CM4 Lite GPIO/RUN_PG: Module1.92 (RUN_PG), TP4.1; also elsewhere on the board
/CM4 Lite GPIO/USB_CC1: J3.A5 (CC1), R27.1
/CM4 Lite GPIO/USB_CC2: J3.B5 (CC2), R24.1
/CM4 Lite GPIO/USB_D+: J3.A6 (D+), J3.B6 (D+), U8.3 (I/O2)
/CM4 Lite GPIO/USB_D-: J3.A7 (D-), J3.B7 (D-), U8.1 (I/O1)
/CM4 Lite GPIO/USB_Do+: R29.2, U8.4 (I/O2)
/CM4 Lite GPIO/USB_Do-: R28.1, U8.6 (I/O1)
/CM4 Lite GPIO/nEXTRST: Module1.100 (nEXTRST), TP5.1; also elsewhere on the board
/CM4 Lite GPIO/nPI_LED_PWR: Module1.95 (nPI_LED_PWR), U9.2 (A)
/CM4 Lite GPIO/nPI_LED_PWR_drain: LED8.1 (K), U9.4 (Y)
/CM4 Lite GPIO/nPI_LED_PWR_r: LED8.2 (A), R42.2
/CM4 Lite GPIO/~SAFEBOOT: TP2.1, U5.50 (~SAFEBOOT)
/GPIO_EXP_~INT: Module1.41 (GPIO25); also elsewhere on the board
/I2C_SCL: Module1.56 (GPIO3), TP12.1; also elsewhere on the board
/I2C_SDA: Module1.58 (GPIO2), TP13.1; also elsewhere on the board
unnamed: D7.1 (K), R26.1
unnamed: LED4.2 (A), R36.2
unnamed: LED4.1 (K), Q3.3 (C)
unnamed: LED6.2 (A), R37.2
unnamed: LED6.1 (K), Q4.3 (C)
unnamed: R22.2, R23.2, U6.8 (OE)

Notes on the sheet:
<-- optional ferrite bead
TXD3
BG95 NET_STATUS LED
1.8V to 3.3V Level Shifter
TXD2
The BG95 can be turned on and off by powering BG95_PWRKEY for 500–1000ms.
dtoverlay needed
BG95 STATUS LED
See datasheet (3.5.1) trace size recomendations
Red
Orange
The ZED-F9P requires a very clean supply. So we use an LDO to avoid ripple.
ZED-F9P Debug USB Receptacle
Status LEDs
50Ω traces
TXD0
RESET is connected internally to PWRKEY
uSIM
50 Ω impedance
uSIM Interface
Green
Active Antenna Bias
Activity LED
BG95 LTE Cell
RTC Battery
Decoupling
RXD2
RXD0
Main F9P LDO
PWRKEY Driver
uSIM (NSIM) Holder
PWM0
CM4 Lite GPIO
Yellow
ZED-F9P-15B GNSS (L1+L5) and Active Antenna
Antenna Outs
PWR LED
V_USB F9P LDO
RXD3

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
